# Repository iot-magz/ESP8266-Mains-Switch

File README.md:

# ESP8266-Mains-Switch
WiFi Mains Switch Using ESP8266

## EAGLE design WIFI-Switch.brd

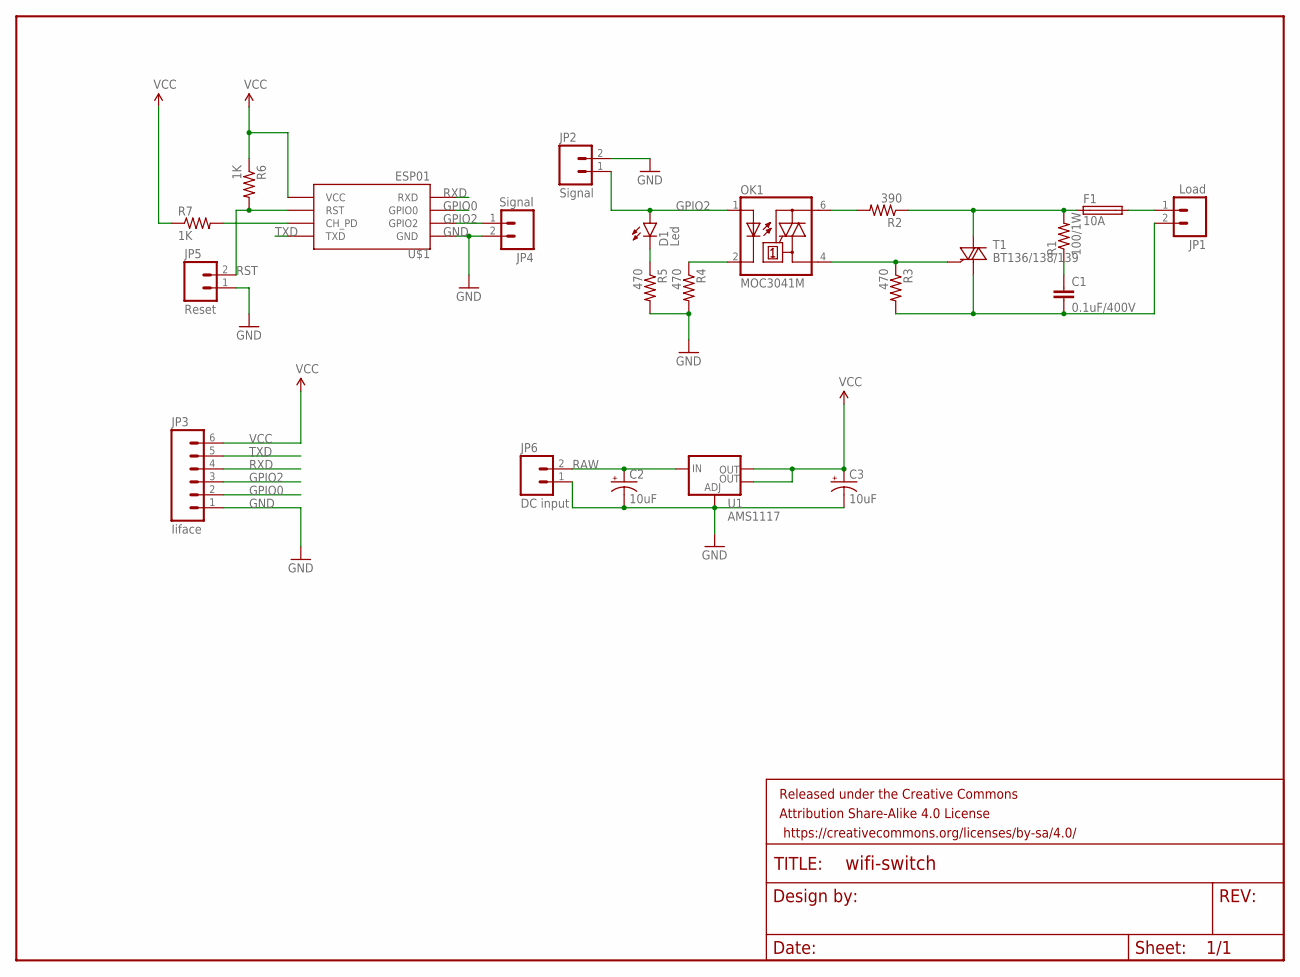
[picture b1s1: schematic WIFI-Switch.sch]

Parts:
C1: 0.1uF/400V; C10B4
C2, C3: 10uF; EIA3216
D1: Led; LED3MM
F1: 10A; SH22,5A
FRAME1: FRAME-LETTER; CREATIVE_COMMONS
JP1: Load; SCREWTERMINAL-5MM-2
JP2, JP4: Signal; 1X02_LOCK
JP3: Iiface; 1X06_FEMALE_LOCK.010
JP5: Reset; 1X02_LOCK
JP6: DC input; 1X02_LOCK
OK1: MOC3041M; DIL06
R1: 100/1W; AXIAL-0.8
R2: 390; AXIAL-0.1
R3: 470; AXIAL-0.4
R4, R5: 470; AXIAL-0.1
R6, R7: 1K; AXIAL-0.1
T1: BT136/138/139; TO220BV
U1: AMS1117; SOT223
U$1: ESP01

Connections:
GND: C2.C (-), C3.C (-), JP2.2, JP3.1, JP4.2, JP5.1, JP6.1, R4.P$2 (2), R5.P$2 (2), U1.1 (ADJ), U$1.GND
GPIO0: JP3.2, U$1.GPIO0
GPIO2: D1.A, JP2.1, JP3.3, JP4.1, OK1.1 (A), U$1.GPIO2
unnamed: F1.2, JP1.1
unnamed: R7.P$2 (2), U$1.CH_PD
unnamed: D1.K (C), R5.P$1 (1)
unnamed: OK1.2 (C), R4.P$1 (1)
unnamed: OK1.6 (A2), R2.P$2 (2)
unnamed: F1.1, R1.P$2 (2), R2.P$1 (1), T1.T2 (A2)
unnamed: OK1.4 (A1), R3.P$1 (1), T1.G
unnamed: C1.2, JP1.2, R3.P$2 (2), T1.T1 (A1)
unnamed: C1.1, R1.P$1 (1)
RAW: C2.A (+), JP6.2, U1.3 (IN)
RST: JP5.2, R6.P$2 (2), U$1.RST
RXD: JP3.4, U$1.RX (RXD)
TXD: JP3.5, U$1.TX (TXD)
VCC: C3.A (+), JP3.6, R6.P$1 (1), R7.P$1 (1), U1.2 (OUT), U1.4 (OUT), U$1.VCC

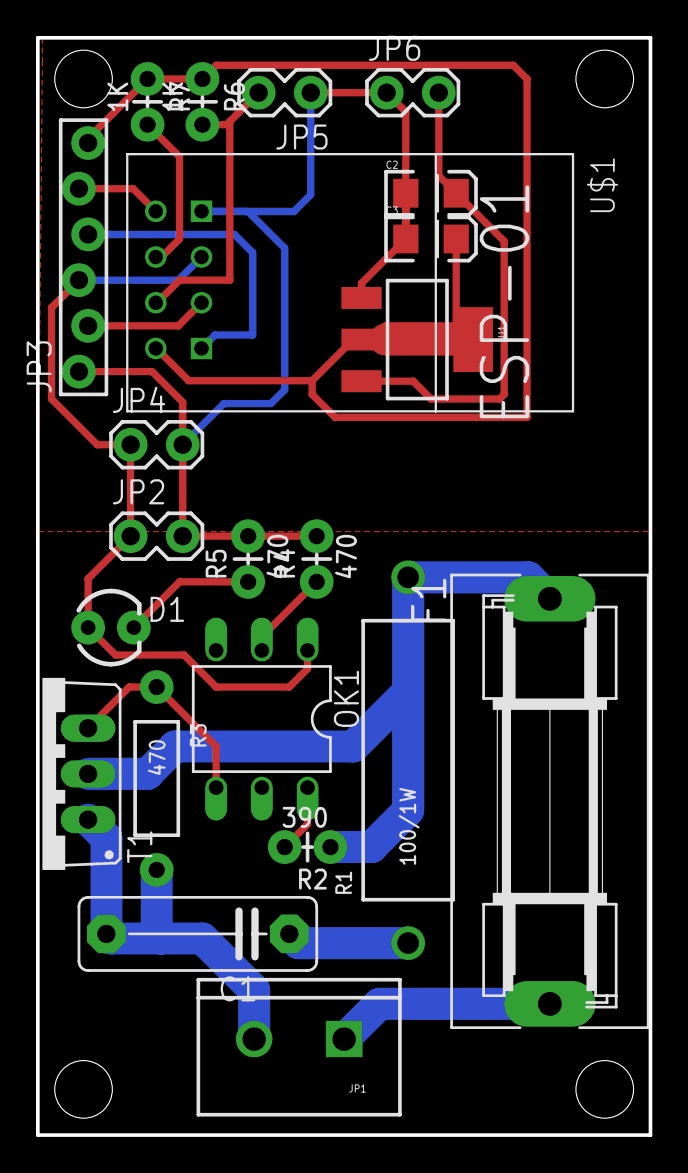
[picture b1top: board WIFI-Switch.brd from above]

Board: 2 copper layers, 34.0 x 61.0 mm, 23 parts (0 on the bottom side), 17 nets.

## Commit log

2016-01-12 update board size
    update board size and components reposition

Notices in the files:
parts and their libraries:
SparkFun-Aesthetics: Licensing: Creative Commons ShareAlike 4.0 International - https://creativecommons.org/licenses/by-sa/4.0
SparkFun-Aesthetics: Released under the Creative Commons Attribution Share-Alike 4.0 License
SparkFun-Aesthetics: https://creativecommons.org/licenses/by-sa/4.0
